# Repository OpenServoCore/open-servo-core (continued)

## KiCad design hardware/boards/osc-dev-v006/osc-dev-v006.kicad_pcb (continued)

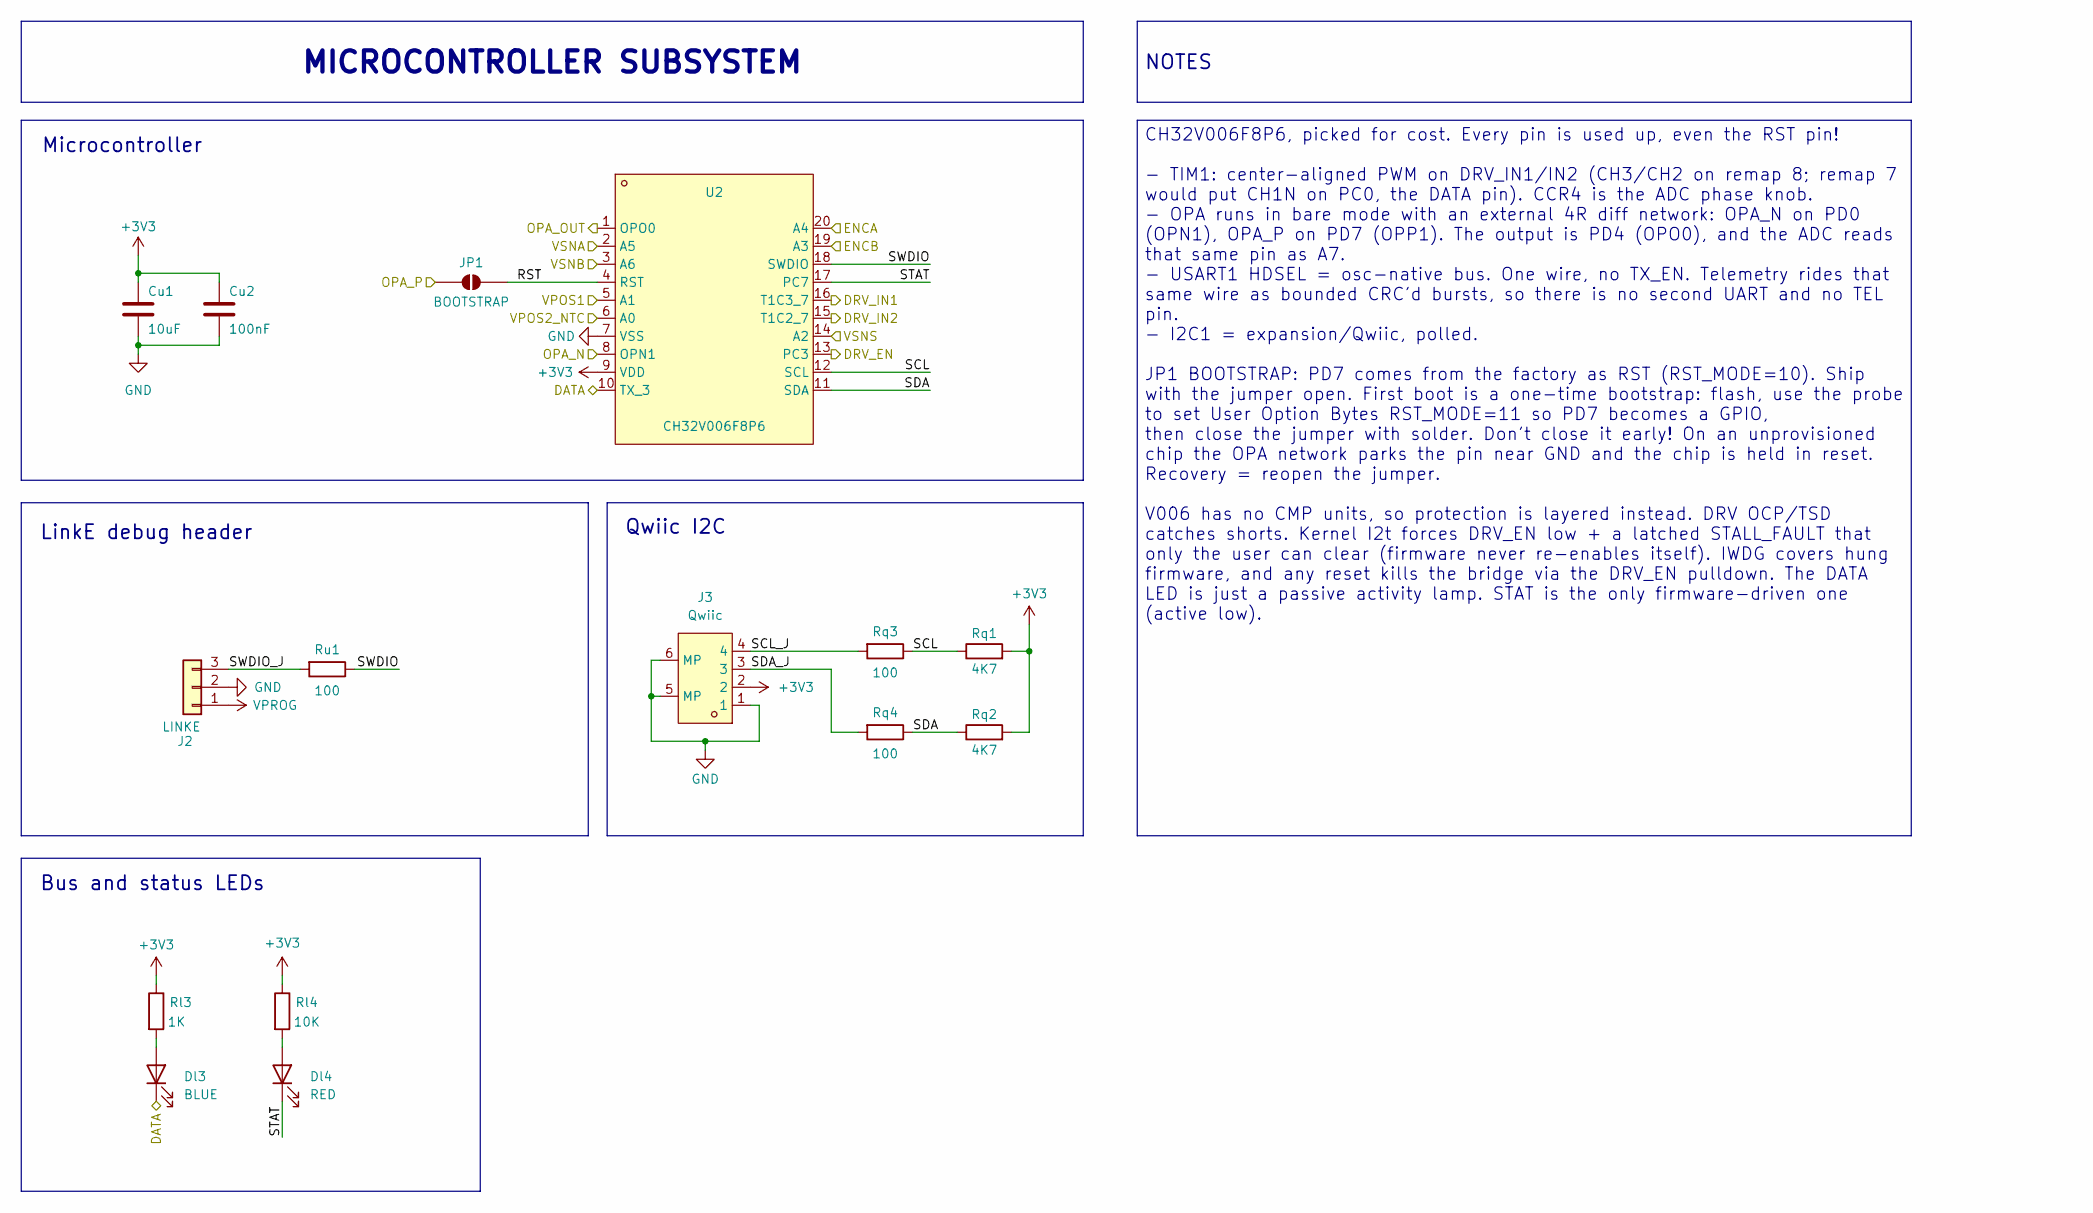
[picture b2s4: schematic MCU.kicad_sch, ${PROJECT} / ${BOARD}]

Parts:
Cu1: 10uF; C_0805_2012Metric_Pad1.18x1.45mm_HandSolder; LCSC C15850
Cu2: 100nF; C_0603_1608Metric_Pad1.08x0.95mm_HandSolder; LCSC C14663
Dl3: BLUE; LED_0603_1608Metric_Pad1.05x0.95mm_HandSolder; LCSC C51933294
Dl4: RED; LED_0603_1608Metric_Pad1.05x0.95mm_HandSolder; LCSC C497918
J2: LINKE; PinHeader_1x03_P2.54mm_Vertical; LCSC C49257
J3: Qwiic; CONN-SMD_SH1.0MM-4P-WT; LCSC C53055320
JP1: BOOTSTRAP; SolderJumper-2_P1.3mm_Open_TrianglePad1.0x1.5mm
Rl3: 1K; R_0603_1608Metric_Pad0.98x0.95mm_HandSolder; LCSC C22548
Rl4: 10K; R_0603_1608Metric_Pad0.98x0.95mm_HandSolder; LCSC C2906982
Rq1, Rq2: 4K7; R_0603_1608Metric_Pad0.98x0.95mm_HandSolder; LCSC C2907034
Rq3, Rq4: 100; R_0603_1608Metric_Pad0.98x0.95mm_HandSolder; LCSC C125923
Ru1: 100; R_0603_1608Metric_Pad0.98x0.95mm_HandSolder; LCSC C125923
U2: CH32V006F8P6; TSSOP-20_4.4x6.5mm_P0.65mm; LCSC C52753342

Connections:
+3V3: Cu1.1, Cu2.1, J3.2, Rl3.1, Rl4.1, Rq1.2, Rq2.2, U2.9 (VDD); also elsewhere on the board
/COMMS/DATA: Dl3.1 (K), U2.10 (TX_3); also elsewhere on the board
/DRV/DRV_EN: U2.13 (PC3); also elsewhere on the board
/DRV/DRV_IN1: U2.16 (T1C3_7); also elsewhere on the board
/DRV/DRV_IN2: U2.15 (T1C2_7); also elsewhere on the board
/MCU/ENCA: U2.20 (A4); also elsewhere on the board
/MCU/ENCB: U2.19 (A3); also elsewhere on the board
/MCU/OPA_N: U2.8 (OPN1); also elsewhere on the board
/MCU/OPA_OUT: U2.1 (OPO0); also elsewhere on the board
/MCU/OPA_P: JP1.1 (A); also elsewhere on the board
/MCU/RST: JP1.2 (B), U2.4 (RST)
/MCU/SCL: Rq1.1, Rq3.1, U2.12 (SCL)
/MCU/SCL_J: J3.4, Rq3.2
/MCU/SDA: Rq2.1, Rq4.1, U2.11 (SDA)
/MCU/SDA_J: J3.3, Rq4.2
/MCU/STAT: Dl4.1 (K), U2.17 (PC7)
/MCU/SWDIO: Ru1.1, U2.18 (SWDIO)
/MCU/SWDIO_J: J2.3, Ru1.2
/MCU/VPOS1: U2.5 (A1); also elsewhere on the board
/MCU/VPOS2_NTC: U2.6 (A0); also elsewhere on the board
/MCU/VSNA: U2.2 (A5); also elsewhere on the board
/MCU/VSNB: U2.3 (A6); also elsewhere on the board
/MCU/VSNS: U2.14 (A2); also elsewhere on the board
GND: Cu1.2, Cu2.2, J2.2, J3.1, J3.5 (MP), J3.6 (MP), U2.7 (VSS); also elsewhere on the board
unnamed: Dl3.2 (A), Rl3.2
unnamed: Dl4.2 (A), Rl4.2
VPROG: J2.1; also elsewhere on the board

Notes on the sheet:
Microcontroller
Qwiic I2C
LinkE debug header
Bus and status LEDs
NOTES
CH32V006F8P6, picked for cost. Every pin is used up, even the RST pin! - TIM1: center-aligned PWM on DRV_IN1/IN2 (CH3/CH2 on remap 8; remap 7 would put CH1N on PC0, the DATA pin). CCR4 is the ADC phase knob. - OPA runs in bare mode with an external 4R diff network: OPA_N on PD0 (OPN1), OPA_P on PD7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
MICROCONTROLLER SUBSYSTEM

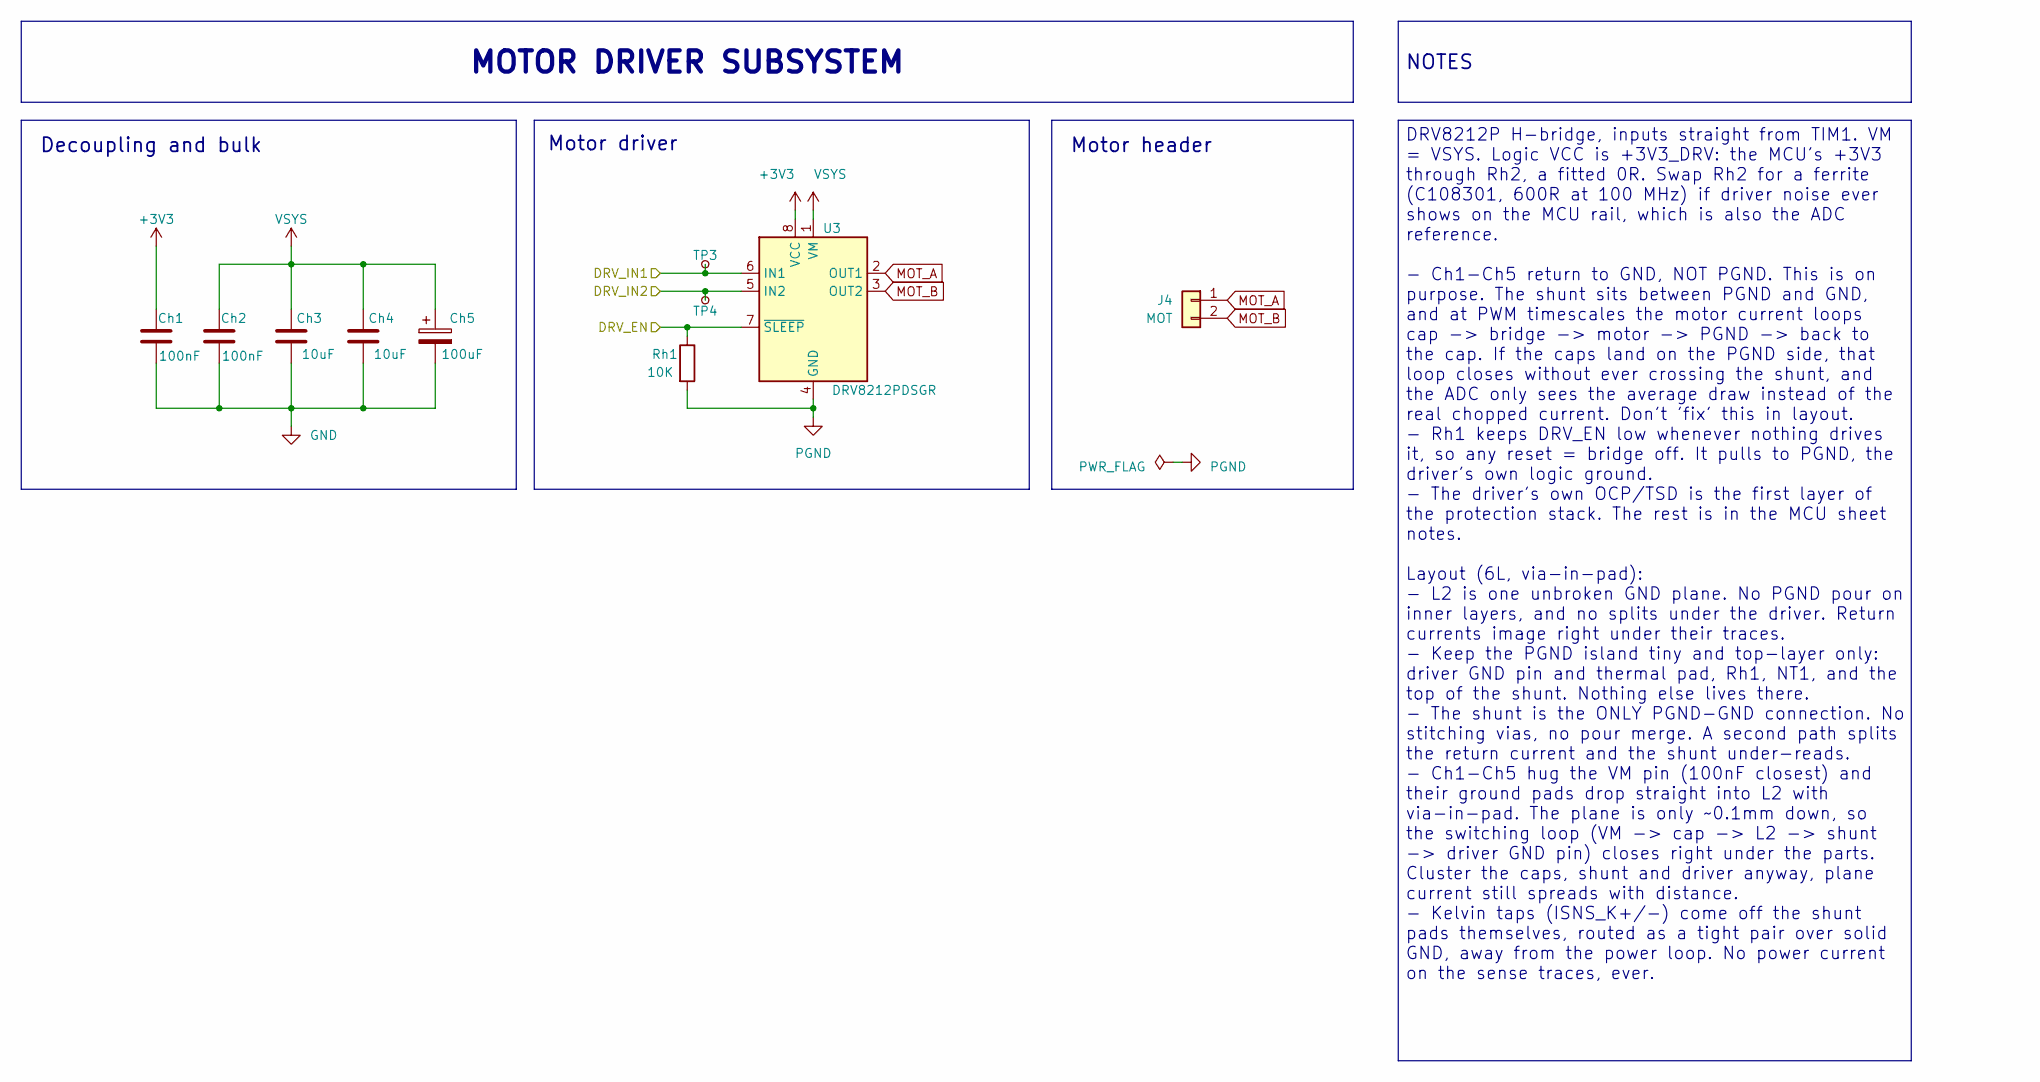
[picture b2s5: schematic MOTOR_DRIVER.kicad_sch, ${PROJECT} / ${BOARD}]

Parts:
Ch1, Ch2: 100nF; C_0603_1608Metric_Pad1.08x0.95mm_HandSolder; LCSC C14663
Ch3, Ch4: 10uF; C_0805_2012Metric_Pad1.18x1.45mm_HandSolder; LCSC C15850
Ch5: 100uF; CP_Elec_6.3x5.4; LCSC C22383777
J4: MOT; PinHeader_1x02_P2.54mm_Vertical; LCSC C492401
Rh1: 10K; R_0603_1608Metric_Pad0.98x0.95mm_HandSolder; LCSC C2906982
TP3: IN1; TestPoint_Pad_D1.0mm
TP4: IN2; TestPoint_Pad_D1.0mm
U3: DRV8212PDSGR; Texas_DSG0008A_WSON-8-1EP_2x2mm_P0.5mm_EP0.9x1.6mm; LCSC C5208051

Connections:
+3V3: Ch1.1, U3.8 (VCC); also elsewhere on the board
/DRV/DRV_EN: Rh1.1, U3.7 (~SLEEP); also elsewhere on the board
/DRV/DRV_IN1: TP3.1 (1_1), U3.6 (IN1); also elsewhere on the board
/DRV/DRV_IN2: TP4.1 (1_1), U3.5 (IN2); also elsewhere on the board
GND: Ch1.2, Ch2.2, Ch3.2, Ch4.2, Ch5.2; also elsewhere on the board
MOT_A: J4.1, U3.2 (OUT1); also elsewhere on the board
MOT_B: J4.2, U3.3 (OUT2); also elsewhere on the board
PGND: Rh1.2, U3.4 (GND), U3.9 (GND); also elsewhere on the board
VSYS: Ch2.1, Ch3.1, Ch4.1, Ch5.1, U3.1 (VM); also elsewhere on the board

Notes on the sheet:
Motor header
Decoupling and bulk
Motor driver
MOTOR DRIVER SUBSYSTEM
NOTES
DRV8212P H-bridge, inputs straight from TIM1. VM = VSYS. Logic VCC is +3V3_DRV: the MCU's +3V3 through Rh2, a fitted 0R. Swap Rh2 for a ferrite (C108301, 600R at 100 MHz) if driver noise ever shows on the MCU rail, which is also the ADC reference. - Ch1-Ch5 return to GND, NOT PGND. This is on purpo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

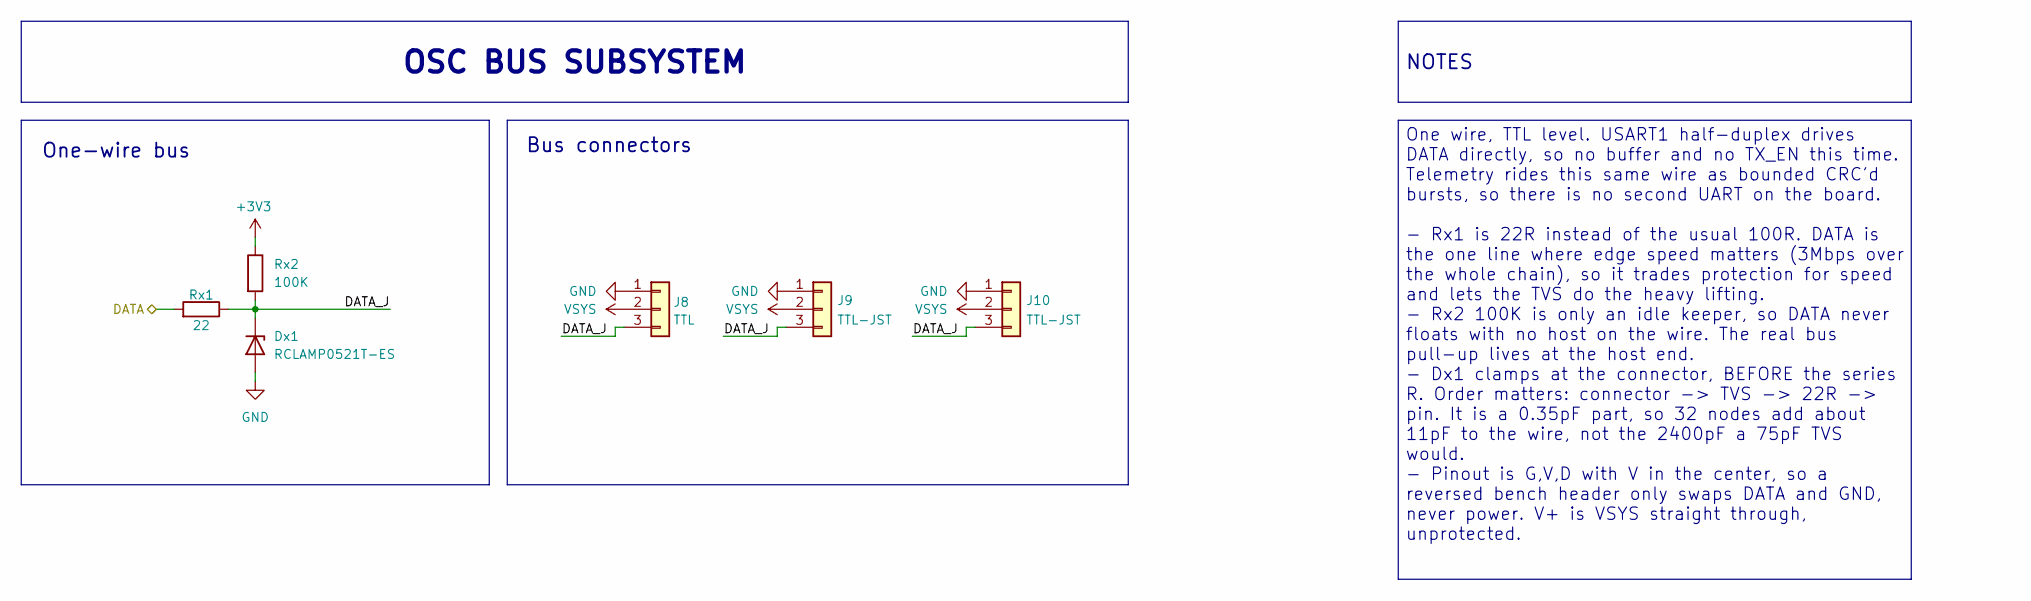
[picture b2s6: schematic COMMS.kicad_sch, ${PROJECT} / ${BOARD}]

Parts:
Dx1: RCLAMP0521T-ES; D_SOD-882; LCSC C5180263
J8: TTL; PinHeader_1x03_P2.54mm_Vertical; LCSC C49257
J9, J10: TTL-JST; CONN-TH_B3B-PH-K-S; LCSC C131339
Rx1: 22; R_0603_1608Metric_Pad0.98x0.95mm_HandSolder; LCSC C203424
Rx2: 100K; R_0603_1608Metric_Pad0.98x0.95mm_HandSolder; LCSC C2906980

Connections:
+3V3: Rx2.1; also elsewhere on the board
/COMMS/DATA: Rx1.2; also elsewhere on the board
/COMMS/DATA_J: Dx1.1 (K), J8.3, J9.3, J10.3, Rx1.1, Rx2.2
GND: Dx1.2 (A), J8.1, J9.1, J10.1; also elsewhere on the board
VSYS: J8.2, J9.2, J10.2; also elsewhere on the board

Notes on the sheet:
Bus connectors
One-wire bus
One wire, TTL level. USART1 half-duplex drives DATA directly, so no buffer and no TX_EN this time. Telemetry rides this same wire as bounded CRC'd bursts, so there is no second UART on the board. - Rx1 is 22R instead of the usual 100R. DATA is the one line where edge speed matters (3Mbps over the w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
OSC BUS SUBSYSTEM
NOTES

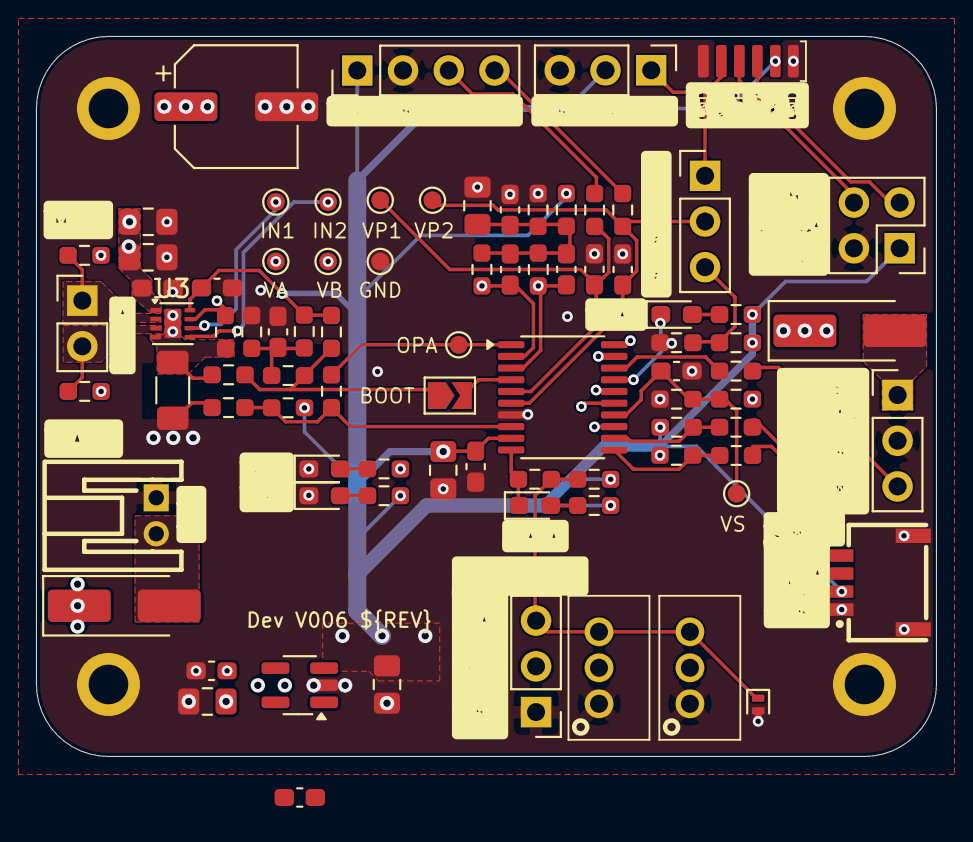
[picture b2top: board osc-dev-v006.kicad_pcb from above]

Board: 4 copper layers, 50.0 x 40.0 mm, 91 parts (0 on the bottom side), 44 nets.

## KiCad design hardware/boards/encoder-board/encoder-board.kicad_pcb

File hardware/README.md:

# KiCad Component Management

## Component Linkage System

### Directory Structure

```
hardware/
├── shared.kicad_sym        # Symbol library
├── shared.pretty/           # Footprint library
├── shared.3dshapes/         # 3D models
├── templates/jlc4l_1v6mm/   # Template project (canonical reference)
└── boards/*/                # Board projects
```

### Linkage Patterns

#### 1. Project → Libraries

Projects link to shared libraries via `sym-lib-table` and `fp-lib-table`:

- Symbol library: `${KIPRJMOD}/../../shared.kicad_sym`
- Footprint library: `${KIPRJMOD}/../../shared.pretty`

#### 2. Symbol → Footprint

Symbols in `shared.kicad_sym` reference footprints using library prefix:

- Format: `"shared:FOOTPRINT_NAME"`
- Example: `"shared:UQFN-20_L3.0-W3.0-P0.40-BL-EP1.7"`

#### 3. Footprint → 3D Model

Footprints in `shared.pretty/` reference 3D models using relative paths:

- Format: `${KIPRJMOD}/../../shared.3dshapes/MODEL_NAME.wrl`
- Example: `${KIPRJMOD}/../../shared.3dshapes/UQFN-20_L3.0-W3.0-P0.40-BL-EP1.7.wrl`

## Component Acquisition Strategy

1. Navigate to a board or template directory:

   ```bash
   cd hardware/templates/jlc4l_1v6mm
   ```

2. Download component:

   ```bash
   easyeda2kicad --full --lcsc_id <LCSC_ID> --output ../../shared --overwrite --project-relative
   ```

3. Fix 3D model paths in footprint files:
   - Find: `${KIPRJMOD}././shared.3dshapes`
   - Replace: `${KIPRJMOD}/../../shared.3dshapes`

4. In `shared.kicad_sym`, rename the `LCSC Part` property to `LCSC` on the downloaded symbol.

## Post-Import Checklist

- [ ] Symbol has correct footprint reference (`"shared:FOOTPRINT_NAME"`)
- [ ] Footprint has correct 3D model path (`${KIPRJMOD}/../../shared.3dshapes/...`)
- [ ] Pin types are correctly set: power_in (VCC/GND), input (control/data in), output (data out), passive (connectors) - NO "unspecified" pins allowed
- [ ] 3D model displays correctly in KiCad 3D viewer
- [ ] Symbol uses `LCSC` property (not `LCSC Part`) for the part number
- [ ] Component source documented (LCSC part number)

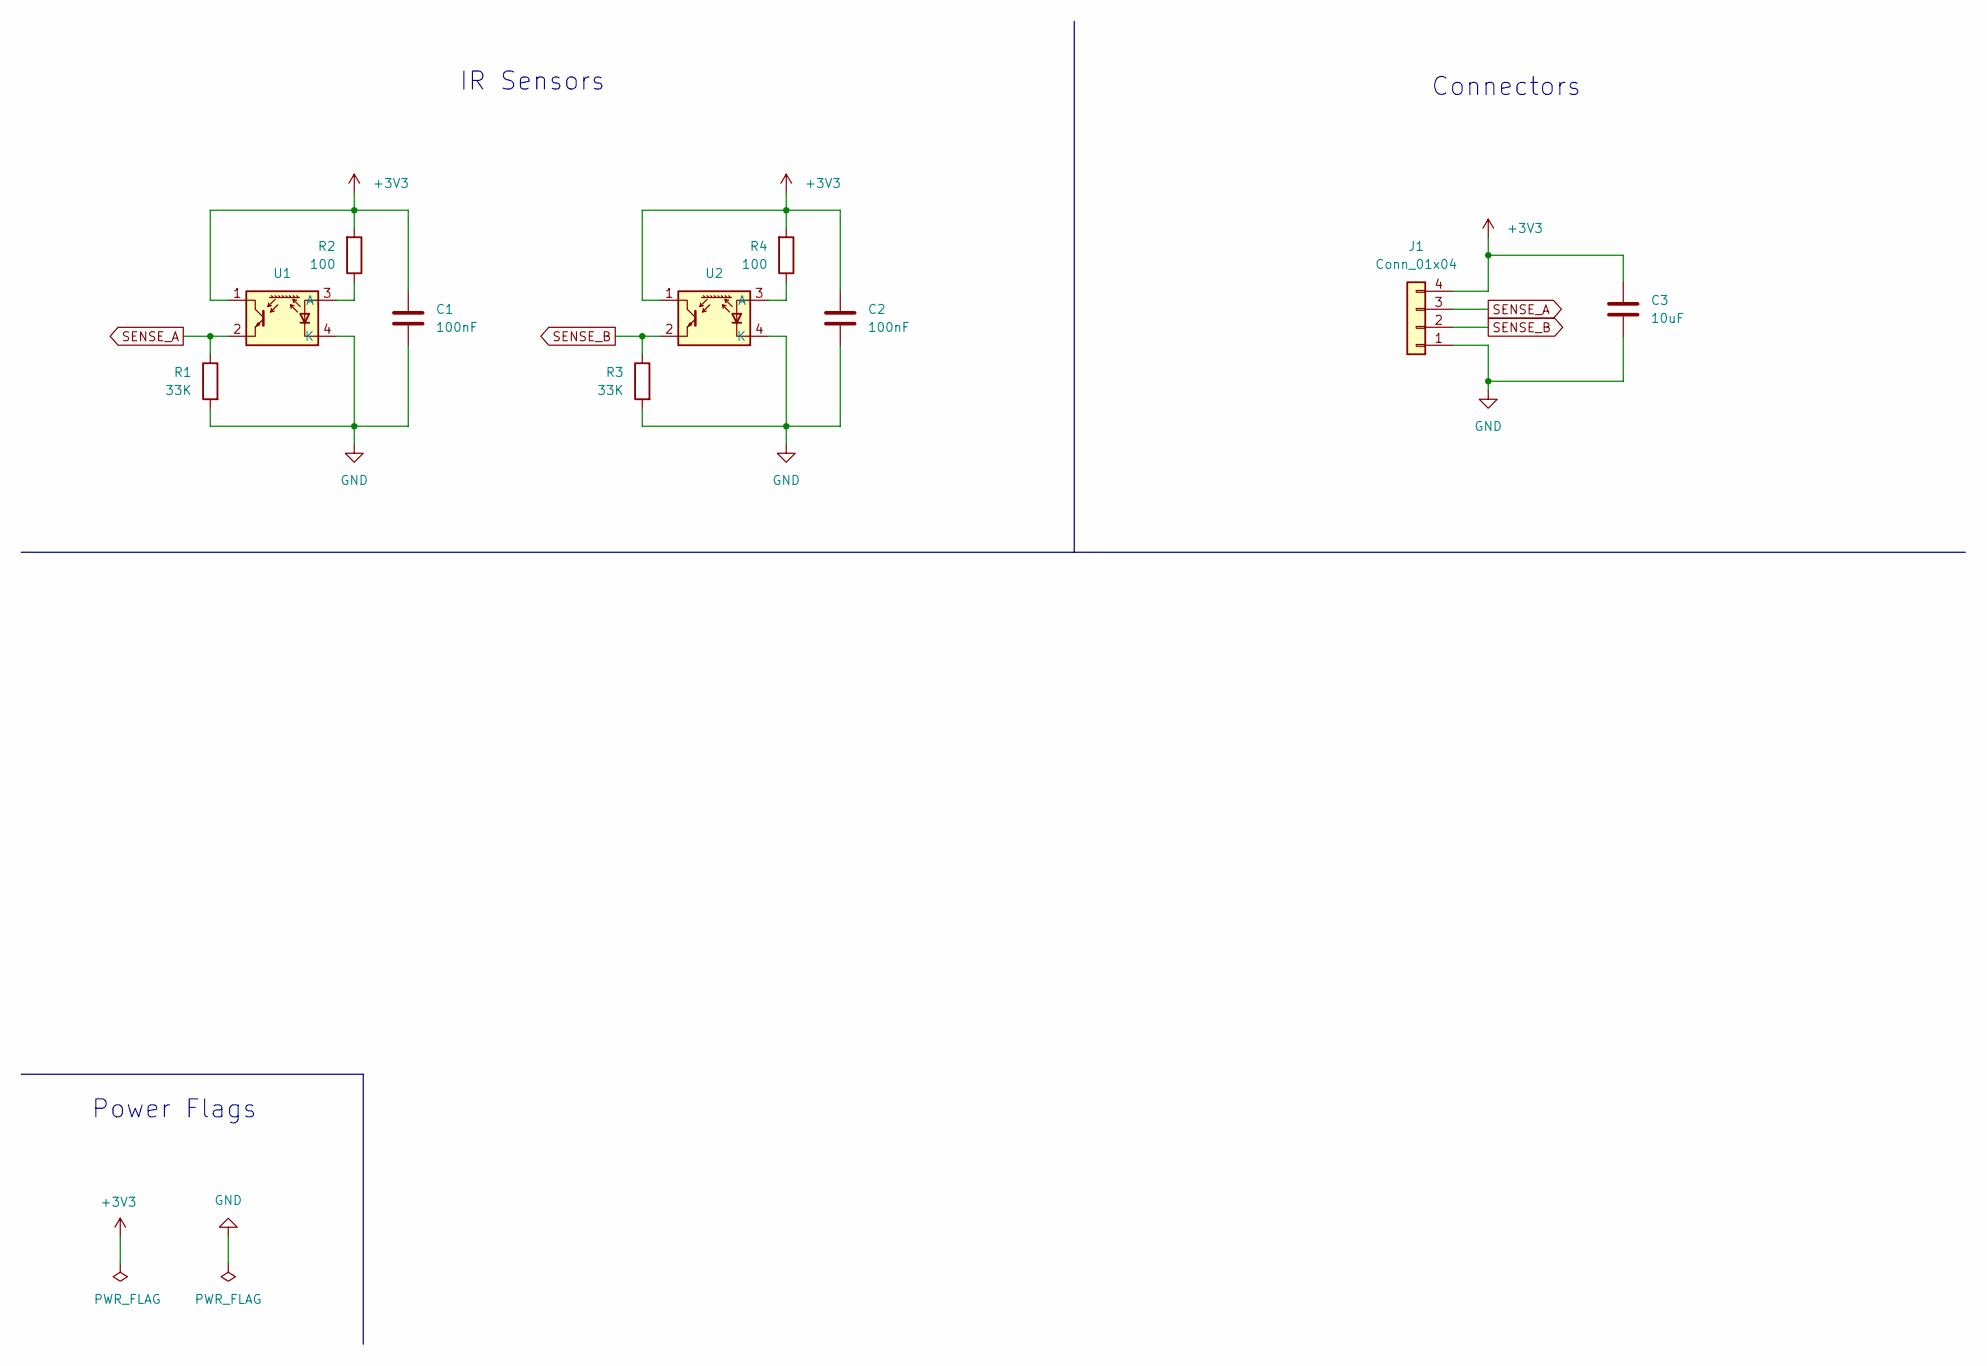
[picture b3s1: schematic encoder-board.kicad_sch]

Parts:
C1, C2: 100nF; C_0805_2012Metric_Pad1.18x1.45mm_HandSolder; LCSC C49678
C3: 10uF; C_0805_2012Metric_Pad1.18x1.45mm_HandSolder; LCSC C15850
J1: Conn_01x04; PinHeader_1x04_P2.54mm_Vertical; LCSC C780062
R1, R3: 33K; R_0805_2012Metric_Pad1.20x1.40mm_HandSolder; LCSC C17633
R2, R4: 100; R_0805_2012Metric_Pad1.20x1.40mm_HandSolder; LCSC C17408
U1, U2: ITR1204SR10A_TR(BY); OPTO-SMD-4_ITR1204SR10A; LCSC C475373

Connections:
+3V3: C1.1, C2.1, C3.1, J1.4, R2.2, R4.2, U1.1, U2.1
GND: C1.2, C2.2, C3.2, J1.1, R1.2, R3.2, U1.4 (K), U2.4 (K)
unnamed: R2.1, U1.3 (A)
unnamed: R4.1, U2.3 (A)
SENSE_A: J1.3, R1.1, U1.2
SENSE_B: J1.2, R3.1, U2.2

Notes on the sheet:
IR Sensors
Connectors
Power Flags

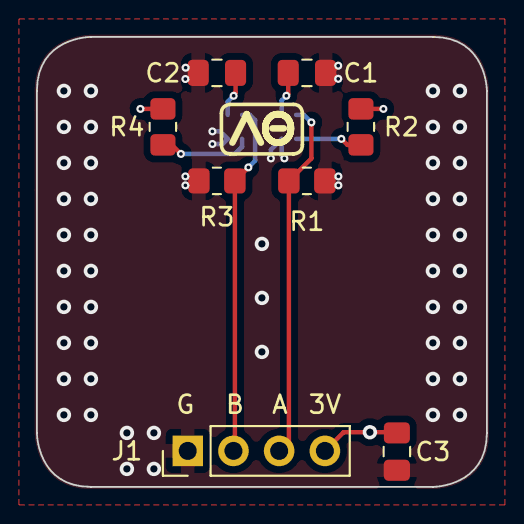
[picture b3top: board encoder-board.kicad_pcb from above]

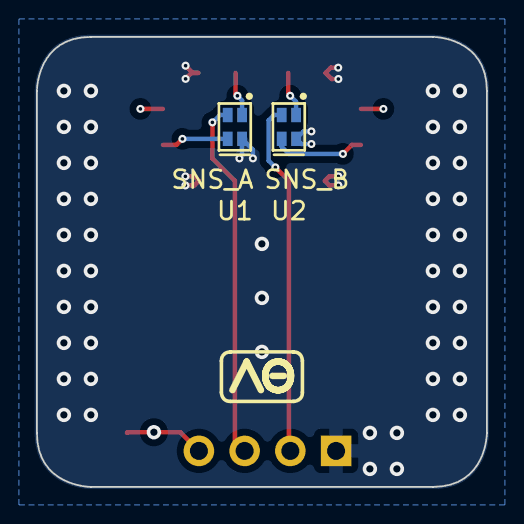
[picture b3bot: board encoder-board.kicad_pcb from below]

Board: 4 copper layers, 25.0 x 25.0 mm, 10 parts (2 on the bottom side), 6 nets.

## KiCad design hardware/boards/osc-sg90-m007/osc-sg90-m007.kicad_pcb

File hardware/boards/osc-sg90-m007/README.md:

# OSC SG90 M007

> ⚠️ **Designed, not spun. Pre-fabrication, pre-bringup.**
> This board has never been fabbed. Numbers and behaviour described below are **design intent**, not measured. The M007 layout is fully routed and DRC-clean, but it exists as a feasibility study - the dev board gets built and validated first. Don't fab this without doing your own review.

OpenServoCore swap board for SG90-class hobby servos. Compact, double-sided, designed to physically replace the factory PCB inside an SG90 case. CH32M007-based: one IC carries the MCU, the 3-phase gate pre-driver, the HV regulator, and the current-sense amplifier - no motor-driver IC, no LDO, no bus buffer.

## Overview

- **MCU + driver** - CH32M007E8U7 (QFN-26, 3×3 mm): 48 MHz RISC-V, integrated gate pre-driver with hardware dead-time, internal HV regulator (VSYS → 5 V VDD), on-die OPA/PGA current sense, CMP overcurrent → TIM1 brake in silicon.
- **Bridge** - 2× MCC MCMNP2065A (dual complementary N+P, DFN2020-6L 2×2 mm; N 20 mΩ / P 44 mΩ @4.5 V), one package per half-bridge, gates driven directly from HO/LO (no gate resistors), 100 kΩ gate keepers. Gates are ±10 V rated: legal because gate drive is rail-limited below the driver's 9.5 V clamp floor - see the 2S pin below.
- **Current shunts** - 2× 75 mΩ 1 % 0.5 W 0805 (Yageo PE series), per-leg low-side, Kelvin taps via net-ties into the on-die PGA (G = 16 differential).
- **Power input** - 6.5-9 V, **2S only** - the bridge's ±10 V gate rating pins this board to 2S (the dev board's 6.5-15 V window needs the ±20 V SOT-23-6 part). Firmware must interlock PWM above ~9 V rail (VSYS reads through the phase dividers). The gate-driver UVLO sets the 6.5 V floor; 1S and USB-5V cannot drive the bridge. VHREG is strapped to VHV (no series resistor).
- **Bus** - single-wire half-duplex UART (osc-native protocol), direct USART HDSEL on PB3 - no buffer. 33 Ω series + PESD5V0L1BA on DATA. 0.5-3 Mbaud.
- **Temperature** - on-board 10 kΩ NTC, B25/50 = 3380 K (NCP15XH103, 0402). Note: the dev board's NTC is 3950 K - the B constant is board-seeded config, not shared firmware math.
- **Position feedback** - existing servo potentiometer wiper, 4.7 kΩ + 100 nF at the ADC pin.
- **Passives** - smallest-package policy: 10 µF and 2.2 µF are 0603, all other R/C are 0402, shunts are the 1206 exception. JLC-basic parts wherever one exists; every part carries `LCSC`, `MFPN`, `Datasheet`, and `JLC_Basic` fields.
- **Form factor** - 10 × 12.5 mm target, double-sided assembly.

## Connectors

### Servo cable - J1 (1×3, wire pads)

Standard hobby-servo 3-wire cable; the signal wire carries the osc-native bus instead of PWM.

Center-power, same order as the dev board's bus connectors - an offset misplug never puts VSYS on DATA.

| Pad | Net    | Notes                       |
| --- | ------ | --------------------------- |
| 1   | `DATA` | Half-duplex osc-native bus. |
| 2   | `VSYS` | 6.5-15 V (2S/3S).           |
| 3   | `GND`  |                             |

### Motor - J2 (2 wire pads)

Solder directly to the SG90 motor leads (phase A / phase B of the bridge).

### Potentiometer - J4 (3 pads)

| Pad   | Net   | Notes              |
| ----- | ----- | ------------------ |
| `+5V` | `+5V` | Pot top rail.      |
| `POT` | `POT` | Wiper, via 4.7 kΩ. |
| `GND` | `GND` | Pot ground.        |

### Debug - J3 (4 pads, 1.0 mm pitch)

Single-wire SWIO for WCH-LinkE (`wlink`).

| Pad | Net    |
| --- | ------ |
| 1   | `+5V`  |
| 2   | `GND`  |
| 3   | `SWIO` |
| 4   | `nRST` |

## Design intent

These are the targets the schematic was drawn around. None are measured.

- **Decoupling** - DS Fig 3-1-3 floor exactly: 10 µF + 0.1 µF (25 V) on VHV, 2.2 µF on VHREG, 10 µF + 0.1 µF on VDD. No bulk beyond that - the single VHV 10 µF (bias-derated ~5 µF at 8.4 V) is the entire on-servo reservoir. This assumes the hub/BEC end of the harness carries the real per-branch bulk; hot-plug onto a charged pack rings a ceramic-only input and is a first-article scope item.
- **Voltage sensing** - 20 kΩ / 10 kΩ dividers on both phases (VSNA/VSNB); 15 V → 5 V at the ADC. Rail voltage reads through the phase dividers with the bridge parked high.
- **Current sensing** - per-leg shunts into the on-die PGA; CMP2 trip window ~2.5-2.75 A between worst 2S stall and harm (range budget in the bringup repo's `osc-dev-m007-pinout.md`).
- **Protection** - PESD5V0X1BCSFYL on DATA (ultra-low-capacitance, DFN1006-2); hardware OCP internal to the M007; no reverse-polarity protection (captive harness).

## Assembly

Double-sided assembly, 0402-and-up, suitable for JLCPCB economic SMT (all jellybeans are basic parts; extended types: MCU, FETs, shunts, PESD, 2.2 µF, 25 V 0402 100 nF, NTC). Motor, pot, and servo-cable connections are hand-soldered wire pads during the servo transplant.

## Mechanical fit

Designed to drop into a standard SG90 servo case. Pad spacing for motor leads and debug pitch are still **to be confirmed against a physical case** when first boards arrive.

## License

Hardware files (schematic, layout, board files in this directory) are licensed under [CERN-OHL-P v2.0](../../../LICENSE-HARDWARE). See the [top-level README](../../../README.md#license) for the full licensing picture.

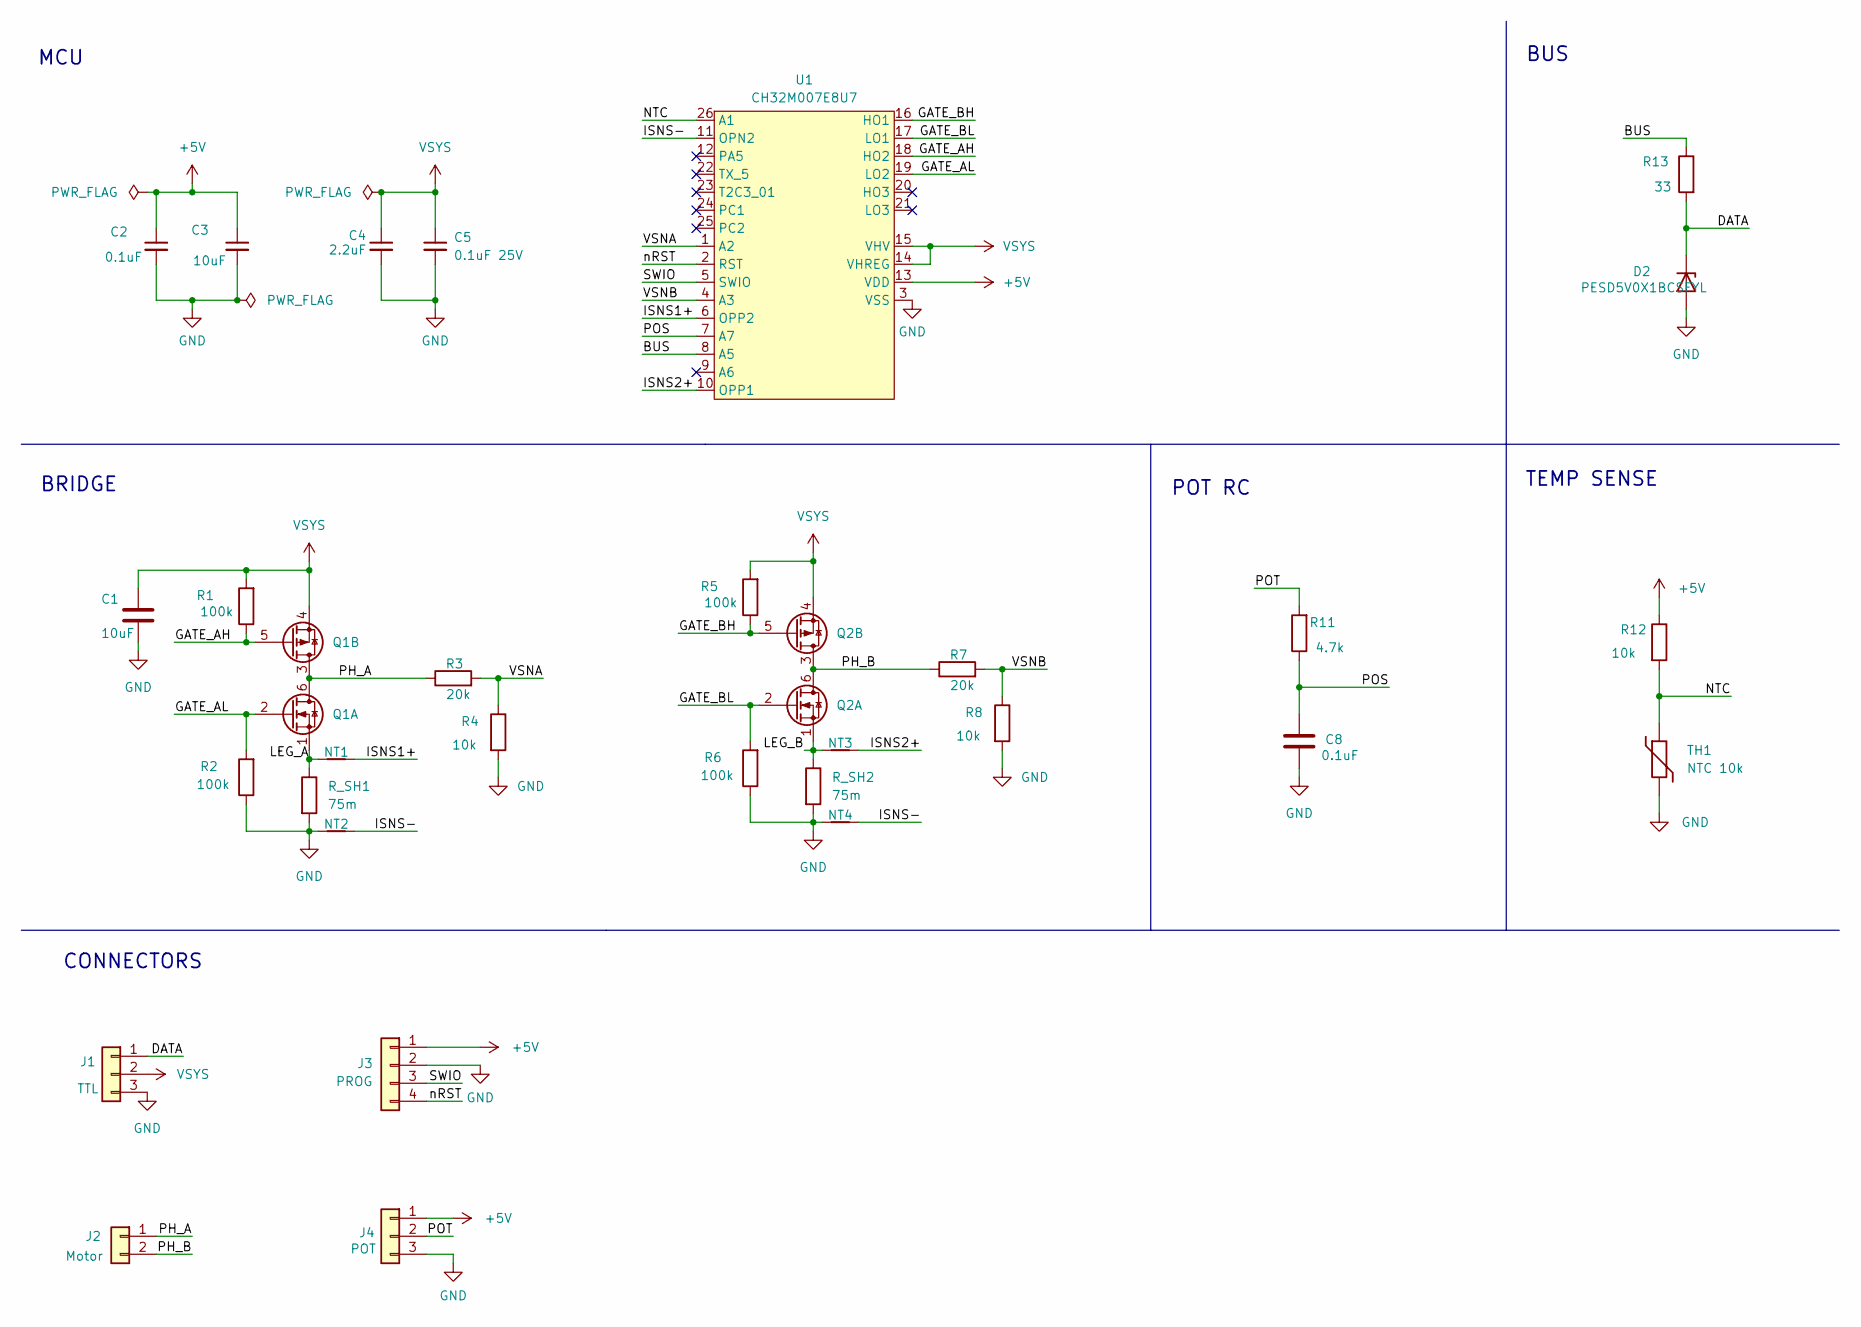
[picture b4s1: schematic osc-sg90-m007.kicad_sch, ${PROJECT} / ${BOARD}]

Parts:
C1, C3: 10uF; C_0603_1608Metric; JLC_Basic yes
C2: 0.1uF; C_0402_1005Metric; JLC_Basic yes
C4: 2.2uF; C_0603_1608Metric; JLC_Basic no
C5: 0.1uF 25V; C_0402_1005Metric; JLC_Basic no
C8: 0.1uF; C_0402_1005Metric; LCSC C1525
D2: PESD5V0X1BCSFYL; D_SOD-882; LCSC C2443412
J1: TTL; Servo_Output_Pads
J2: Motor; Motor_Wire_Pads
J3: PROG; Debug_Pads_1x4_P1.0mm
J4: POT; Pot_Wire_Pads
NT1, NT2, NT3, NT4: NetTie_2; NetTie-2_SMD_0.127mm
Q1, Q2: MCMNP2065A-TP; DFN2020-6L; JLC_Basic no
R1, R2, R5, R6: 100k; R_0402_1005Metric; JLC_Basic yes
R3, R7: 20k; R_0402_1005Metric; LCSC C25765
R4, R8, R12: 10k; R_0402_1005Metric; LCSC C25744
R11: 4.7k; R_0402_1005Metric; LCSC C25900
R13: 33; R_0402_1005Metric; LCSC C25105
R_SH1, R_SH2: 75m; R_0603_1608Metric; JLC_Basic no
TH1: NTC 10k; R_0402_1005Metric; LCSC C77131
U1: CH32M007E8U7; QFN-26_3x3mm_P0.4mm; JLC_Basic no

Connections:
+5V: C2.1, C3.1, J3.1, J4.1, R12.1, U1.13 (VDD)
/BUS: R13.1, U1.8 (A5)
/DATA: D2.1 (K), J1.1, R13.2
/GATE_AH: Q1.5 (G), R1.1, U1.18 (HO2)
/GATE_AL: Q1.2 (G), R2.2, U1.19 (LO2)
/GATE_BH: Q2.5 (G), R5.1, U1.16 (HO1)
/GATE_BL: Q2.2 (G), R6.2, U1.17 (LO1)
/ISNS1+: NT1.2, U1.6 (OPP2)
/ISNS2+: NT3.2, U1.10 (OPP1)
/ISNS-: NT2.2, NT4.2, U1.11 (OPN2)
/LEG_A: NT1.1, Q1.1 (S), R_SH1.1
/LEG_B: NT3.1, Q2.1 (S), R_SH2.1
/NTC: R12.2, TH1.1, U1.26 (A1)
/PH_A: J2.1, Q1.3 (D), Q1.6 (D), R3.1
/PH_B: J2.2, Q2.3 (D), Q2.6 (D), R7.1
/POS: C8.1, R11.1, U1.7 (A7)
/POT: J4.2, R11.2
/SWIO: J3.3, U1.5 (SWIO)
/VSNA: R3.2, R4.1, U1.1 (A2)
/VSNB: R7.2, R8.1, U1.4 (A3)
/nRST: J3.4, U1.2 (RST)
GND: C1.2, C2.2, C3.2, C4.2, C5.2, C8.2, D2.2 (A), J1.3, J3.2, J4.3, NT2.1, NT4.1, R2.1, R4.2, R6.1, R8.2, R_SH1.2, R_SH2.2, TH1.2, U1.3 (VSS)
VSYS: C1.1, C4.1, C5.1, J1.2, Q1.4 (S), Q2.4 (S), R1.2, R5.2, U1.14 (VHREG), U1.15 (VHV)

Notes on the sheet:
CONNECTORS
TEMP SENSE
BUS
MCU
POT RC
BRIDGE

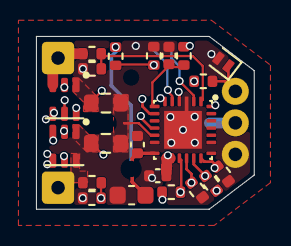
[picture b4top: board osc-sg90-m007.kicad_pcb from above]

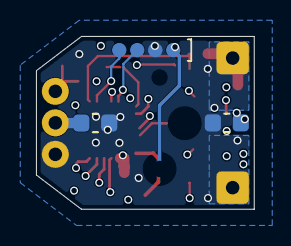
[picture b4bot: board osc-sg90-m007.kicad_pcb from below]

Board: 6 copper layers, 12.1 x 9.6 mm, 32 parts (3 on the bottom side), 23 nets.
